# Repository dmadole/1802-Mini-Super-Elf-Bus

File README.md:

# 1802-Mini-Super-Elf-Bus-Adapter
This is a bus adapter card for the Quest Super Elf that adapts it to expansion cards for the [1802/Mini](https://github.com/dmadole/1802-Mini) system. It supports the following features:

* Connects to 50-pin expansion connector on Super Elf
* 64K of memory in two 32K RAM, EPROM, or EEPROM devices
* Supports 62C64, 62C256, 27C64, 27C256, 28C64, 28C256
* Can temporarily map a ROM at $8000 to $0000 with M key
* TTL level port with Q and selectable EF pin for soft serial
* Transmit and receive polarity selectable on serial port
* Buffered data bus for reliability across ribbon cable
* Additional pull-up resistors for improved rise time on inputs
* Voltage regulator allows powing expansion cards from Super Elf
* Mini-USB connector for independent 5 volt power input
* Form factor allows stacking or backplane by connector choice
* Highly annoted silkscreen documents most settings and pins

Gerber files for the PCBs and PDF schematics can be found in [Releases](https://github.com/dmadole/1802-Mini-Super-Elf-Bus/releases).

BOMS and any applicable errata or other notes can be found in [notes](https://github.com/dmadole/1802-Mini-Super-Elf-Bus/tree/main/notes).

For availability of kits and bare PCBs please see http://madole.net/1802/mini/kits

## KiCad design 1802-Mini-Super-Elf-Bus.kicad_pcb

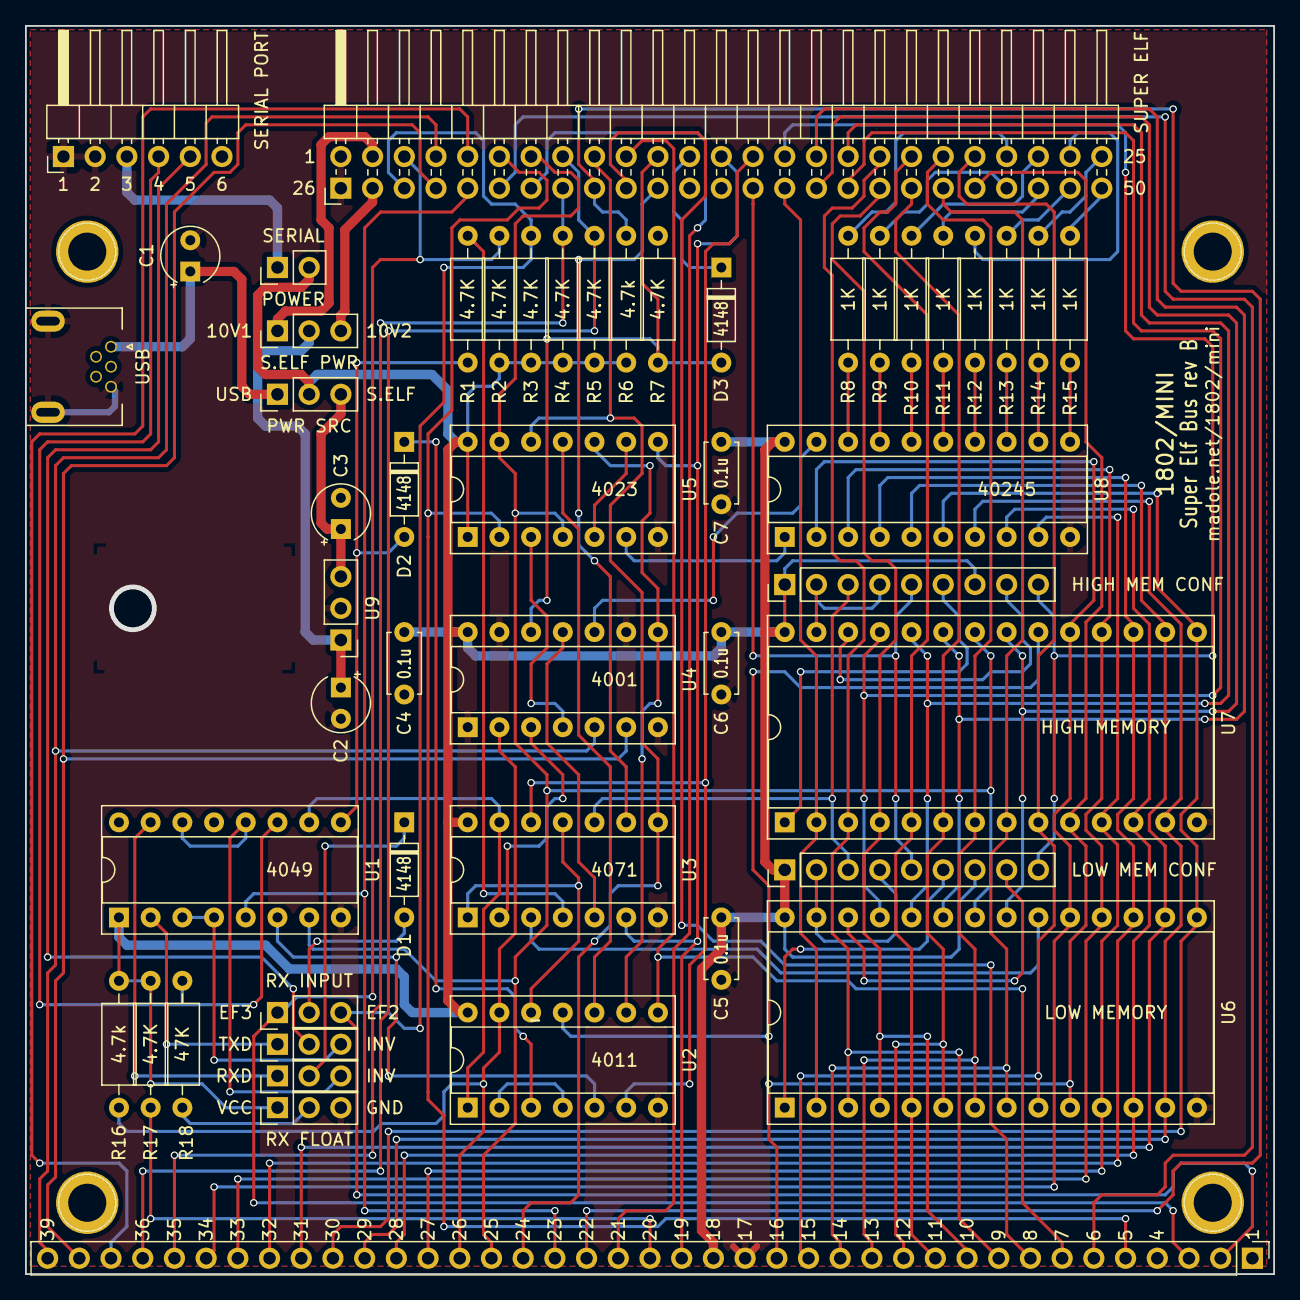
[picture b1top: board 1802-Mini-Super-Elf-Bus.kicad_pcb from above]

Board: 2 copper layers, 100.0 x 100.0 mm, 54 parts (0 on the bottom side), 103 nets.

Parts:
C1: 10uF; CP_Radial_Tantal_D4.5mm_P2.50mm
C2: 0.47uF; CP_Radial_Tantal_D4.5mm_P2.50mm
C3: 22uF; CP_Radial_Tantal_D4.5mm_P2.50mm
C4, C5, C6, C7: 0.1u; C_Disc_D4.7mm_W2.5mm_P5.00mm
D1, D2, D3: 4148; D_DO-35_SOD27_P7.62mm_Horizontal
J1, J2, J3, J4: Mount; 1pin
J5: 1802/Mini Bus; PinHeader_1x39_P2.54mm_Vertical
J6: SLOT_1_CONFIG; PinHeader_1x09_P2.54mm_Vertical
J7: Super Elf Bus; PinHeader_2x25_P2.54mm_Horizontal_Row1_Row2
J8: USB PWR; USB_Mini-AB_Molex_56579_0519
J9: Serial Port; PinHeader_1x06_P2.54mm_Horizontal
J10: SLOT_2_CONFIG; PinHeader_1x09_P2.54mm_Vertical
JP1: POWER; PinHeader_1x02_P2.54mm_Vertical
JP2, JP3: PWR SRC; PinHeader_1x03_P2.54mm_Vertical
JP8: TX_INV; PinHeader_1x03_P2.54mm_Vertical
JP9: RX_SEL; PinHeader_1x03_P2.54mm_Vertical
JP10: RX_INV; PinHeader_1x03_P2.54mm_Vertical
JP11: RX_IDL; PinHeader_1x03_P2.54mm_Vertical
R1, R2, R3, R4, R5, R6, R17: 4.7K; R_Axial_DIN0207_L6.3mm_D2.5mm_P10.16mm_Horizontal
R7, R16: 4.7k; R_Axial_DIN0207_L6.3mm_D2.5mm_P10.16mm_Horizontal
R8, R9, R10, R11, R12, R13, R14, R15: 1K; R_Axial_DIN0207_L6.3mm_D2.5mm_P10.16mm_Horizontal
R18: 47K; R_Axial_DIN0207_L6.3mm_D2.5mm_P10.16mm_Horizontal
U1: 4049; DIP-16_W7.62mm_Socket
U2: 4011; DIP-14_W7.62mm_Socket
U3: 4071; DIP-14_W7.62mm_Socket
U4: 4001; DIP-14_W7.62mm_Socket
U5: 4023; DIP-14_W7.62mm_Socket
U6: LO_MEM; DIP-28_W15.24mm_Socket
U7: HI_MEM; DIP-28_W15.24mm_Socket
U8: 40245; DIP-20_W7.62mm_Socket
U9: LM2940CT; PinHeader_1x03_P2.54mm_Vertical

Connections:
10V1: J7.27, JP2.1
10V2: J7.2, JP2.3
/A0: J5.16, J7.21, U6.10, U7.10
/A1: J5.15, J7.46, U6.9, U7.9
/A2: J5.14, J7.20, U6.8, U7.8
/A3: J5.13, J7.45, U6.7, U7.7
/A4: J5.12, J7.19, U6.6, U7.6
/A5: J5.11, J7.44, U6.5, U7.5
/A6: J5.10, J7.18, U6.4, U7.4
/A7: J5.9, J7.43, U6.3, U7.3
/A8: J7.17, U6.25, U7.25
/A9: J7.42, U6.24, U7.24
/A10: J7.16, U6.21, U7.21
/A11: J7.41, U6.23, U7.23
/A12: J7.15, U6.2, U7.2
/A13: J6.9, J7.40, J10.9
/A14: J6.5, J7.14, J10.5
/BUS0: J5.27, U6.11, U7.11, U8.9
/BUS1: J5.28, U6.12, U7.12, U8.8
/BUS2: J5.29, U6.13, U7.13, U8.7
/BUS3: J5.30, U6.15, U7.15, U8.6
/BUS4: J5.31, U6.16, U7.16, U8.5
/BUS5: J5.32, U6.17, U7.17, U8.4
/BUS6: J5.33, U6.18, U7.18, U8.3
/BUS7: J5.34, U6.19, U7.19, U8.2
/D0: J7.25, R15.2
/D1: J7.50, R14.2
/D2: J7.24, R13.2
/D3: J7.49, R12.2
/D4: J7.23, R11.2
/D5: J7.48, R10.2
/D6: J7.22, R9.2
/D7: J7.47, R8.2
A15: J7.39, U2.6, U3.12
CLOCK: J5.21, J7.7
DIR: U5.6, U8.1
G: D3.1, J7.37
GND: C1.2, C2.2, C3.2, C4.2, C5.2, C6.2, C7.2, J5.17, J7.1, J7.26, J8.5, J8.6, J9.1, J9.2, JP11.3, R7.1, U1.8, U2.7, U3.7, U4.1, U4.7, U4.9, U4.13, U5.7, U6.14, U7.14, U8.10, U9.2
M: D3.2, J7.36, R7.2, U4.12
MEN: J5.26, R16.1, U2.13, U4.2
MP: J7.11, U3.9
N0: J5.39, J7.29, U4.5
N1: J5.38, J7.4, U4.6
N2: J5.37, J7.30
unnamed: C1.1, J8.1, JP3.1
unnamed: C2.1, JP2.2, U9.1
unnamed: C3.1, JP3.3, U9.3
unnamed: D1.1, JP10.2
unnamed: D1.2, JP9.2
unnamed: D2.1, U2.3
unnamed: D2.2, R1.2, U1.9
unnamed: J6.2, J6.4, U6.27
unnamed: J6.6, U6.1
unnamed: J6.8, U6.26
unnamed: J9.3, JP1.1
unnamed: J9.4, R18.2, U1.11
unnamed: J9.5, JP8.2
unnamed: J10.2, J10.4, U7.27
unnamed: J10.6, U7.1
unnamed: J10.8, U7.26
unnamed: JP8.1, U1.2
unnamed: JP8.3, U1.3, U1.4
unnamed: JP10.1, U1.15
unnamed: JP10.3, U1.12, U1.14
unnamed: JP11.2, R18.1
unnamed: R1.1, U3.4
unnamed: R8.1, U8.18
unnamed: R9.1, U8.17
unnamed: R10.1, U8.16
unnamed: R11.1, U8.15
unnamed: R12.1, U8.14
unnamed: R13.1, U8.13
unnamed: R14.1, U8.12
unnamed: R15.1, U8.11
unnamed: U1.6, U2.5
unnamed: U1.10, U2.1, U3.13
unnamed: U2.2, U2.4
unnamed: U2.9, U4.8, U5.10
unnamed: U2.10, U5.11
unnamed: U2.12, U3.1, U3.11
unnamed: U3.2, U4.3
unnamed: U3.5, U4.11
unnamed: U4.4, U5.3
unnamed: U5.5, U5.9
Q: J5.23, J7.5, U1.5
SC0: J5.6, J7.6
SC1: J5.5, J7.31, U5.2
TPA: J5.8, J7.10
TPB: J5.7, J7.35, U2.8
VCC: C4.1, C5.1, C6.1, C7.1, J5.18, J6.1, J6.7, J10.1, J10.7, JP1.2, JP3.2, JP11.1, R2.1, R3.1, R4.1, R5.1, R6.1, R16.2, R17.1, U1.1, U2.14, U3.14, U4.14, U5.1, U5.14, U6.28, U7.28, U8.20
~CLEAR: J5.19, J7.38, U3.6, U5.8
~CS_HI: U2.11, U7.20
~CS_LO: U3.3, U6.20
~DMAIN: J5.36, J7.33, R5.2
~DMAOUT: J5.35, J7.8, R4.2
~EF2: J5.2, J7.3, JP9.3, R3.2
~EF3: J5.3, J7.28, JP9.1, R2.2
~INT: J5.22, J7.9, R6.2
~MRD: J5.25, J7.32, U1.7, U5.4, U5.13, U6.22, U7.22
~MWR: J5.24, J7.34, U3.8, U5.12
~OE: U4.10, U8.19
~WAIT: J5.20, R17.2
~WE: J6.3, J10.3, U3.10

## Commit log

2021-12-17 Rev B updates
2022-02-04 Remove irrelevant reference to Q LED
